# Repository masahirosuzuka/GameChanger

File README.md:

GameChanger
===========

Open Source Hardware Tablet PC

* Android
* AM335x (Cortrex-A8)
* 2GB DDR3-SDRAM
* USB x 2
* LAN
* uSD boot

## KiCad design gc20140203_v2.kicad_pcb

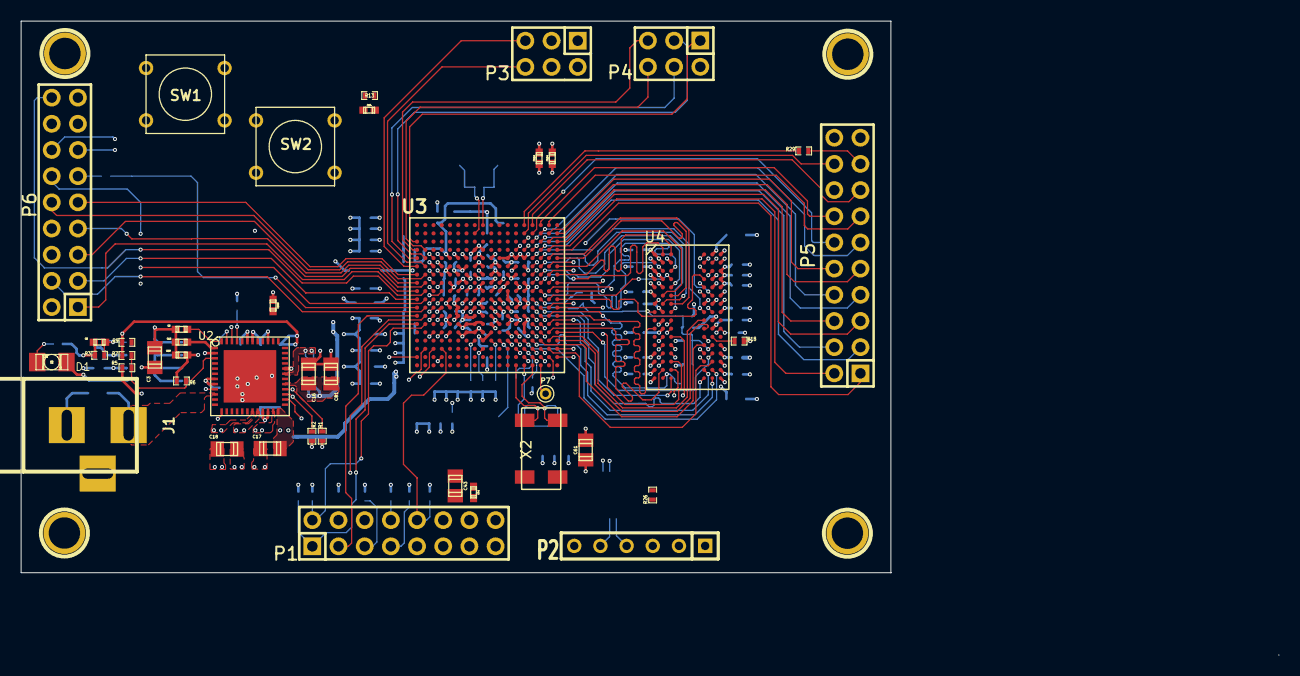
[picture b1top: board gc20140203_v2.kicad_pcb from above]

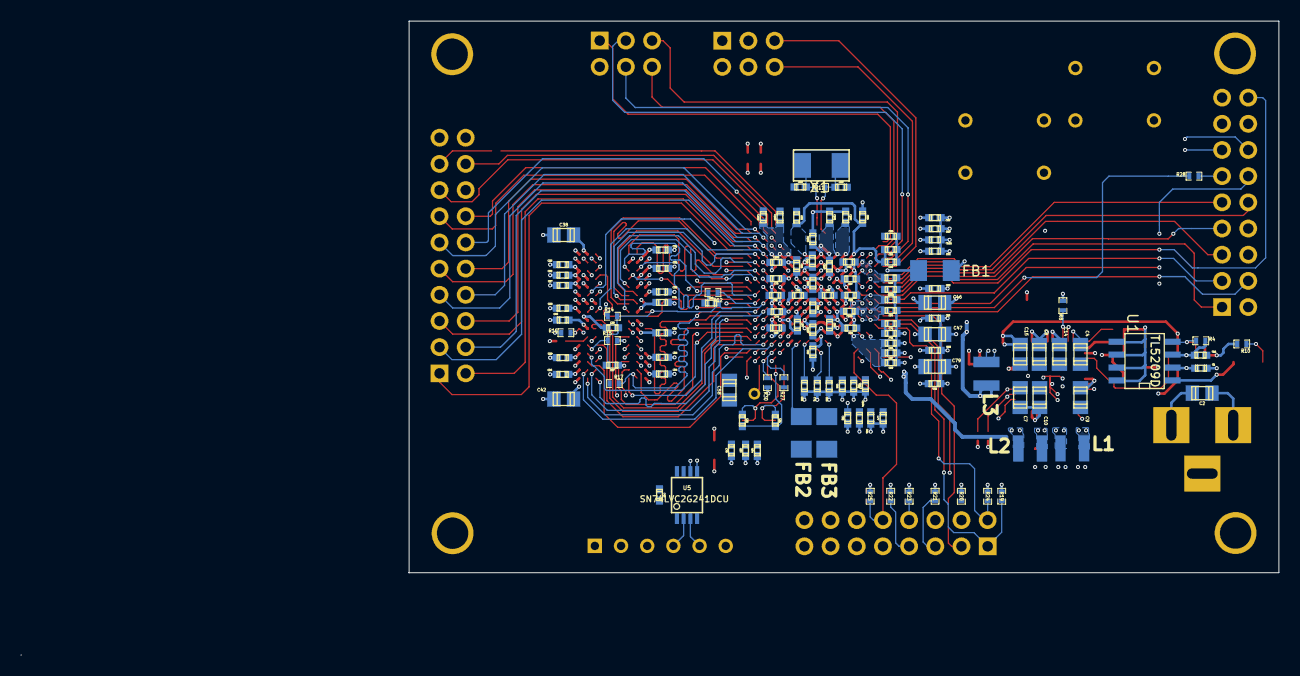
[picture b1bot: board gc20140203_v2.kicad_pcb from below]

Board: 6 copper layers, 84.4 x 53.5 mm, 173 parts (127 on the bottom side), 153 nets.

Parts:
C1, C12, C13: 2.2uF,6.3V; c_0402
C2, C3, C4, C7, C8, C9, C10, C14, C15, C16, C17, C18, C38, C42, C43, C46, C47, C58, C61, C79, C81: 10uF,10V; c_0805
C5: 470pF,6.3V; c_0402
C6: 0.1uF,3V; c_0402
C11, C23, C25, C26, C27, C28, C29, C30, C31, C32, C33, C34, C36, C37, C39, C40, C41, C44, C45, C48, C49, C50, C51, C52, C53, C54, C55, C56, C57, C59, C60, C62, C63, C64, C66, C67, C69, C70, C72, C73, C74, C75, C76, C77, C78, C80, C82, C83, C84, C85, C86, C87, C88, C89, C90, C91, C92, C93, C94, C95, C96, C97, C98, C99, C100, C101, C102, C103, C104, C105, C106, C107, C108, C109, C110, C111, C112, C113, C114, C115: 0.1uF,6.3V; c_0402
C19, C20, C21, C22: 18pF,50V; c_0402
C24, C65, C68, C71: 1uF,10V; c_0402
C35: 0.001uF,50V; c_0402
D1: LED; LED-1206
FB1, FB2, FB3: 150OHM,800mA; Fuse_SMD1206_Wave
J1: JACK_2P; BARREL_JACK
L1, L2, L3: 2.2UH,20%,1300MA,1008; Neosid_Inductor_SM-NE29_SMD1008
P1: USD; Pin_Header_Straight_2x08
P2: Serial; SIL-6
P3: USB0; Pin_Header_Straight_2x03
P4: USB1; Pin_Header_Straight_2x03
P5: LCD_HEADER; Pin_Header_Straight_2x10
P6: LAN_HEADER; Pin_Header_Straight_2x09
P7: CONN_1; PINTST
P8, P9, P10, P11: CONN_1; 1pin
R1, R2, R17: 1.5K,1%; SM0402
R3: 470K,1%; SM0402
R4: 280K,1%; SM0402
R5, R6, R9: 0.1%; SM0402
R7: 0,DNI; SM0402
R8, R26: 100K,1%; SM0402
R10: 4.75K,5%; SM0402
R11: 1M,1%; SM0402
R12: 49.9,1%; SM0402
R13, R14, R15, R16, R19, R20, R21, R22, R23, R24, R25, R30: 10K,1%; SM0402
R18: 240; SM0402
R27: 4.75K,1%; SM0402
R28: 33; SM0402
R29: 22; SM0402
SW1, SW2: SW_PUSH; SW_PUSH_SMALL
U1: TL5209D; SOIC-8_N
U2: TPC65217C; QFN48+1
U3: AM3359AZCZ100; BGA324_0.8mm
U4: MT41K256M16HA-125:E; BGA96-0.8
U5: SN74LVC2G241DCU; MSOP-8
X1: 24MHz; 7A
X2: CM200C

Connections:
3V3: C11.1, C12.1, C14.1, C43.1, C44.1, C45.2, C59.1, C86.2, C87.1, C89.2, C91.2, C93.1, C95.2, C98.2, C100.2, C102.2, C103.2, C105.2, C106.2, C107.1, C108.2, C109.2, C111.1, C112.2, C113.1, C114.2, C115.2, D1.1, P1.4, R1.1, R2.1, R4.2, R8.1, R13.1, R19.1, R20.1, R21.1, R22.1, R23.1, R24.1, R25.2, U1.1, U1.3, U2.1, U2.43, U3.E10, U3.E11, U3.E12, U3.E13, U3.F14, U3.G14, U3.H14, U3.J14, U3.K14, U3.L14, U3.N5, U3.N15, U3.P5, U3.P6, U3.P7, U3.P8, U3.P10, U3.P11, U3.P12, U3.P13, U3.R15, U3.R16, U5.7, U5.8
+0.675V: C23.1, C35.1, C37.1, R14.2, R15.1, U3.J4, U4.H1, U4.M8
+1.1V: C16.1, C17.1, C46.1, C47.1, C48.1, C49.1, C50.1, C52.1, C53.1, C55.1, C57.1, C60.1, C63.1, C66.1, C69.1, C72.1, C74.1, C76.1, C79.1, C81.1, C82.1, C83.1, C84.1, L2.2, L3.2, U2.24, U2.29, U3.A2, U3.F6, U3.F7, U3.F10, U3.F11, U3.F12, U3.F13, U3.G6, U3.G7, U3.G10, U3.G13, U3.H11, U3.H13, U3.J12, U3.J13, U3.K6, U3.K8, U3.K12, U3.L6, U3.L7, U3.L8, U3.L9, U3.M11, U3.M13, U3.N8, U3.N9, U3.N12, U3.N13
+1.8V: C13.1, C15.1, C51.1, C54.1, C56.1, C62.1, C77.1, C85.1, C88.1, C90.1, C94.1, C96.1, C97.1, C99.1, C101.1, C110.1, FB1.1, FB1.2, FB2.2, R5.2, R6.2, R7.1, R9.1, R9.2, R27.1, U2.18, U2.40, U3.D7, U3.D10, U3.E6, U3.E7, U3.E9, U3.E14, U3.F9, U3.H15, U3.K13, U3.N6, U3.N16, U3.P14, U3.R10, U3.R11
+1.35V: C18.1, C25.1, C26.1, C27.1, C28.1, C29.1, C30.1, C31.1, C32.1, C33.1, C34.1, C36.1, C38.1, C39.1, C40.1, C41.1, C42.1, C58.1, C61.1, C64.1, C67.1, C70.1, C73.1, C75.1, C78.1, C80.1, L1.2, R14.1, R17.1, U2.19, U3.E5, U3.F5, U3.G5, U3.H5, U3.J5, U3.K5, U3.L5, U4.A1, U4.A8, U4.B2, U4.C1, U4.C9, U4.D2, U4.D9, U4.E9, U4.F1, U4.G7, U4.H2, U4.H9, U4.K2, U4.K8, U4.N1, U4.N9, U4.R1, U4.R9
+5V: C1.1, C2.1, C3.1, C7.2, C8.1, C9.2, C10.2, J1.1, U1.2, U2.2, U2.7, U2.8, U2.10, U2.12, U2.21, U2.22, U2.32, U2.39, U2.42
/processor1/DDR_A0: U3.F3, U4.N3
/processor1/DDR_A1: U3.H1, U4.P7
/processor1/DDR_A2: U3.E4, U4.P3
/processor1/DDR_A3: U3.C3, U4.N2
/processor1/DDR_A4: U3.C2, U4.P8
/processor1/DDR_A5: U3.B1, U4.P2
/processor1/DDR_A6: U3.D5, U4.R8
/processor1/DDR_A7: U3.E2, U4.R2
/processor1/DDR_A8: U3.D4, U4.T8
/processor1/DDR_A9: U3.C1, U4.R3
/processor1/DDR_A10: U3.F4, U4.L7
/processor1/DDR_A11: U3.F2, U4.R7
/processor1/DDR_A12: U3.E3, U4.N7
/processor1/DDR_A13: U3.H3, U4.T3
/processor1/DDR_A14: U3.H4, U4.T7
/processor1/DDR_A15: U3.D3, U4.M7
/processor1/DDR_BA0: U3.C4, U4.M2
/processor1/DDR_BA1: U3.E1, U4.N8
/processor1/DDR_BA2: U3.B3, U4.M3
/processor1/DDR_D0: U3.M3, U4.E3
/processor1/DDR_D1: U3.M4, U4.F7
/processor1/DDR_D2: U3.N1, U4.F2
/processor1/DDR_D3: U3.N2, U4.F8
/processor1/DDR_D4: U3.N3, U4.H3
/processor1/DDR_D5: U3.N4, U4.H8
/processor1/DDR_D6: U3.P3, U4.G2
/processor1/DDR_D7: U3.P4, U4.H7
/processor1/DDR_D8: U3.J1, U4.D7
/processor1/DDR_D9: U3.K1, U4.C3
/processor1/DDR_D10: U3.K2, U4.C8
/processor1/DDR_D11: U3.K3, U4.C2
/processor1/DDR_D12: U3.K4, U4.A7
/processor1/DDR_D13: U3.L3, U4.A2
/processor1/DDR_D14: U3.L4, U4.B8
/processor1/DDR_D15: U3.M1, U4.A3
/processor1/LDO_PGOOD: U2.46, U3.B15
/processor1/PMIC_INT: R8.2, U2.45, U3.B18
/processor1/PMIC_PGOOD: U2.26, U3.B5
/processor1/ddr3_memory/DDR_CASn: U3.F1, U4.K3
/processor1/ddr3_memory/DDR_CKE: R16.2, U3.G3, U4.K9
/processor1/ddr3_memory/DDR_CLK: U3.D2, U4.J7
/processor1/ddr3_memory/DDR_CLKn: U3.D1, U4.K7
/processor1/ddr3_memory/DDR_CSn: U3.H2, U4.L2
/processor1/ddr3_memory/DDR_DQM0: U3.M2, U4.E7
/processor1/ddr3_memory/DDR_DQM1: U3.J2, U4.D3
/processor1/ddr3_memory/DDR_DQS0: U3.P1, U4.F3
/processor1/ddr3_memory/DDR_DQS1: U3.L1, U4.C7
/processor1/ddr3_memory/DDR_DQSN0: U3.P2, U4.G3
/processor1/ddr3_memory/DDR_DQSN1: U3.L2, U4.B7
/processor1/ddr3_memory/DDR_ODT: U3.G1, U4.K1
/processor1/ddr3_memory/DDR_RASn: U3.G4, U4.J3
/processor1/ddr3_memory/DDR_RESETn: R17.2, U3.G2, U4.T2
/processor1/ddr3_memory/DDR_WEn: U3.B2, U4.L3
/processor1/uSD/MMC0_CLK: P1.5, R21.2, U3.G17
/processor1/uSD/MMC0_CMD: P1.3, R20.2, U3.G18
/processor1/uSD/MMC0_DAT0: P1.7, R22.2, U3.G16
/processor1/uSD/MMC0_DAT1: P1.8, R23.2, U3.G15
/processor1/uSD/MMC0_DAT2: P1.1, R19.2, U3.F18
/processor1/uSD/MMC0_DAT3: P1.2, R24.2, U3.F17
/processor2/I2C0_SCL: R1.2, U2.28, U3.C16
/processor2/I2C0_SDA: R2.2, U2.27, U3.C17
/processor2/LCD_DATA0: P5.1, U3.R1
/processor2/LCD_DATA1: P5.2, U3.R2
/processor2/LCD_DATA2: P5.3, U3.R3
/processor2/LCD_DATA3: P5.4, U3.R4
/processor2/LCD_DATA4: P5.5, U3.T1
/processor2/LCD_DATA5: P5.6, U3.T2
/processor2/LCD_DATA6: P5.7, U3.T3
/processor2/LCD_DATA7: P5.8, U3.T4
/processor2/LCD_DATA8: P5.9, U3.U1
/processor2/LCD_DATA9: P5.10, U3.U2
/processor2/LCD_DATA10: P5.11, U3.U3
/processor2/LCD_DATA11: P5.12, U3.U4
/processor2/LCD_DATA12: P5.13, U3.V2
/processor2/LCD_DATA13: P5.14, U3.V3
/processor2/LCD_DATA14: P5.15, U3.V4
/processor2/LCD_DATA15: P5.16, U3.T5
/processor2/LCD_DE: P5.20, U3.R6
/processor2/LCD_HSYNC: P5.19, U3.R5
/processor2/LCD_PCLK: P5.17, R29.2
/processor2/LCD_VSYNC: P5.18, U3.U5
/processor2/MDIO_CLK: P6.9, U3.M18
/processor2/MDIO_DATA: P6.10, U3.M17
/processor2/MII1_COL: P6.15, U3.H16
/processor2/MII1_CRS_DV: P6.4, U3.H17
/processor2/MII1_REFCLK: P6.11, R28.2
/processor2/MII1_RXCLK: P6.5, U3.L18
/processor2/MII1_RXD0: P6.14, U3.M16
/processor2/MII1_RXD1: P6.6, U3.L15
/processor2/MII1_RXD2: P6.13, U3.L16
/processor2/MII1_RXD3: P6.7, U3.L17
/processor2/MII1_RXDV: P6.8, U3.J17
/processor2/MII1_RXERR: P6.12, U3.J15
/processor2/MII1_TXCLK: P6.1, U3.K18
/processor2/MII1_TXD0: P6.18, U3.K17
/processor2/MII1_TXD1: P6.2, U3.K16
/processor2/MII1_TXD2: P6.17, U3.K15
/processor2/MII1_TXD3: P6.3, U3.J18
/processor2/MII1_TXEN: P6.16, U3.J16
/processor2/PMIC_POWER_EN: U2.9, U3.C6
/processor2/USB0_CE: P3.4, U3.M15
/processor2/USB0_DM: P3.5, U3.N18
/processor2/USB0_DP: P3.6, U3.N17
/processor2/USB0_DRVBUS: P3.2, U3.F16
/processor2/USB0_ID: P3.3, U3.P16
/processor2/USB0_VBUS: P3.1, U3.P15
/processor2/USB1_CE: P4.4, U3.P18
/processor2/USB1_DP: P4.6, U3.R17
/processor2/USB1_DRVBUS: P4.2, U3.F15
/processor2/USB1_ID: P4.3, U3.P17
/processor2/USB1_VBUS: P4.1, U3.T18
/processor2/USb1_DM: P4.5, U3.R18
/processor2/WAKEUP: R27.2, U2.13, U3.C5
AGND: U3.A7, U3.A8, U3.A9, U3.B6, U3.B7, U3.B8, U3.B9, U3.C7, U3.C8, U3.C9
DGND: C1.2, C2.2, C3.2, C4.1, C5.2, C6.1, C7.1, C8.2, C9.1, C10.1, C11.2, C12.2, C13.2, C14.2, C15.2, C16.2, C17.2, C18.2, C19.2, C20.1, C23.2, C24.2, C25.2, C26.2, C27.2, C28.2, C29.2, C30.2, C31.2, C32.2, C33.2, C34.2, C35.2, C36.2, C37.2, C38.2, C39.2, C40.2, C41.2, C42.2, C43.2, C44.2, C45.1, C46.2, C47.2, C48.2, C49.2, C50.2, C51.2, C52.2, C53.2, C54.2, C55.2, C56.2, C57.2, C58.2, C59.2, C60.2, C61.2, C62.2, C63.2, C64.2, C65.2, C66.2, C67.2, C68.2, C69.2, C70.2, C71.2, C72.2, C73.2, C74.2, C75.2, C76.2, C77.2, C78.2, C79.2, C80.2, C81.2, C82.2, C83.2, C84.2, C85.2, C86.1, C87.2, C88.2, C89.1, C90.2, C91.1, C92.2, C93.2, C94.2, C95.1, C96.2, C97.2, C98.1, C99.2, C100.1, C101.2, C102.1, C103.1, C105.1, C106.1, C107.2, C108.1, C109.1, C110.2, C111.2, C112.1, C113.2, C114.1, C115.1, FB3.2, J1.2, J1.3, P1.6, P1.9, P1.11, P1.12, P1.13, P1.14, P1.15, P1.16, P2.1, P8.1, P9.1, P10.1, P11.1, R3.1, R10.2, R12.2, R15.2, R16.1, R18.2, R26.2, R30.2, SW1.1, SW2.1, U1.5, U1.6, U1.7, U1.8, U2.30, U2.41, U2.49, U3.A1, U3.A18, U3.F8, U3.G8, U3.G9, U3.G11, U3.G12, U3.H6, U3.H7, U3.H8, U3.H9, U3.H10, U3.H12, U3.J6, U3.J7, U3.J8, U3.J9, U3.J10, U3.J11, U3.K7, U3.K9, U3.K10, U3.K11, U3.L10, U3.L11, U3.L12, U3.L13, U3.M6, U3.M7, U3.M8, U3.M9, U3.M10, U3.M12, U3.M14, U3.N7, U3.N10, U3.N11, U3.N14, U3.V1, U3.V11, U3.V18, U4.A9, U4.B1, U4.B3, U4.B9, U4.D1, U4.D8, U4.E1, U4.E2, U4.E8, U4.F9, U4.G1, U4.G8, U4.G9, U4.J2, U4.J8, U4.M1, U4.M9, U4.P1, U4.P9, U4.T1, U4.T9, U5.1, U5.4
GNDA: C104.2, FB3.1, U3.E8
MMC0_CD: P1.10, R25.1, U3.C15
unnamed: C4.2, U2.47
unnamed: C5.1, R3.2, R4.1, U1.4
unnamed: C6.2, U2.48
unnamed: C19.1, R11.1, U3.V10, X1.2
unnamed: C20.2, R11.2, U3.U11, X1.1
unnamed: C21.1, C22.1, U3.A5
unnamed: C21.2, U3.A6, X2.4
unnamed: C22.2, U3.A4, X2.1
unnamed: C24.1, R13.2, SW2.2, U3.A10
unnamed: C65.1, U3.D9
unnamed: C68.1, U3.D11
unnamed: C71.1, U3.C10
unnamed: C92.1, U3.D6
unnamed: C104.1, FB2.1, U3.D8
unnamed: D1.2, R10.1
unnamed: L1.1, U2.20
unnamed: L2.1, U2.23
unnamed: L3.1, U2.31
unnamed: P2.4, R26.1, U5.2
unnamed: P2.5, U5.3
unnamed: P7.1, U3.A3
unnamed: R5.1, R6.1, R7.2, U2.3
unnamed: R12.1, U3.J3
unnamed: R18.1, U4.L8
unnamed: R28.1, U3.H18
unnamed: R29.1, U3.V5
unnamed: R30.1, U3.B4
unnamed: SW1.2, U2.25
unnamed: U3.E15, U5.6
unnamed: U3.E16, U5.5

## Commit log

2014-06-06 Power supply
2014-06-07 PWR layer
2014-06-08 GND layer
